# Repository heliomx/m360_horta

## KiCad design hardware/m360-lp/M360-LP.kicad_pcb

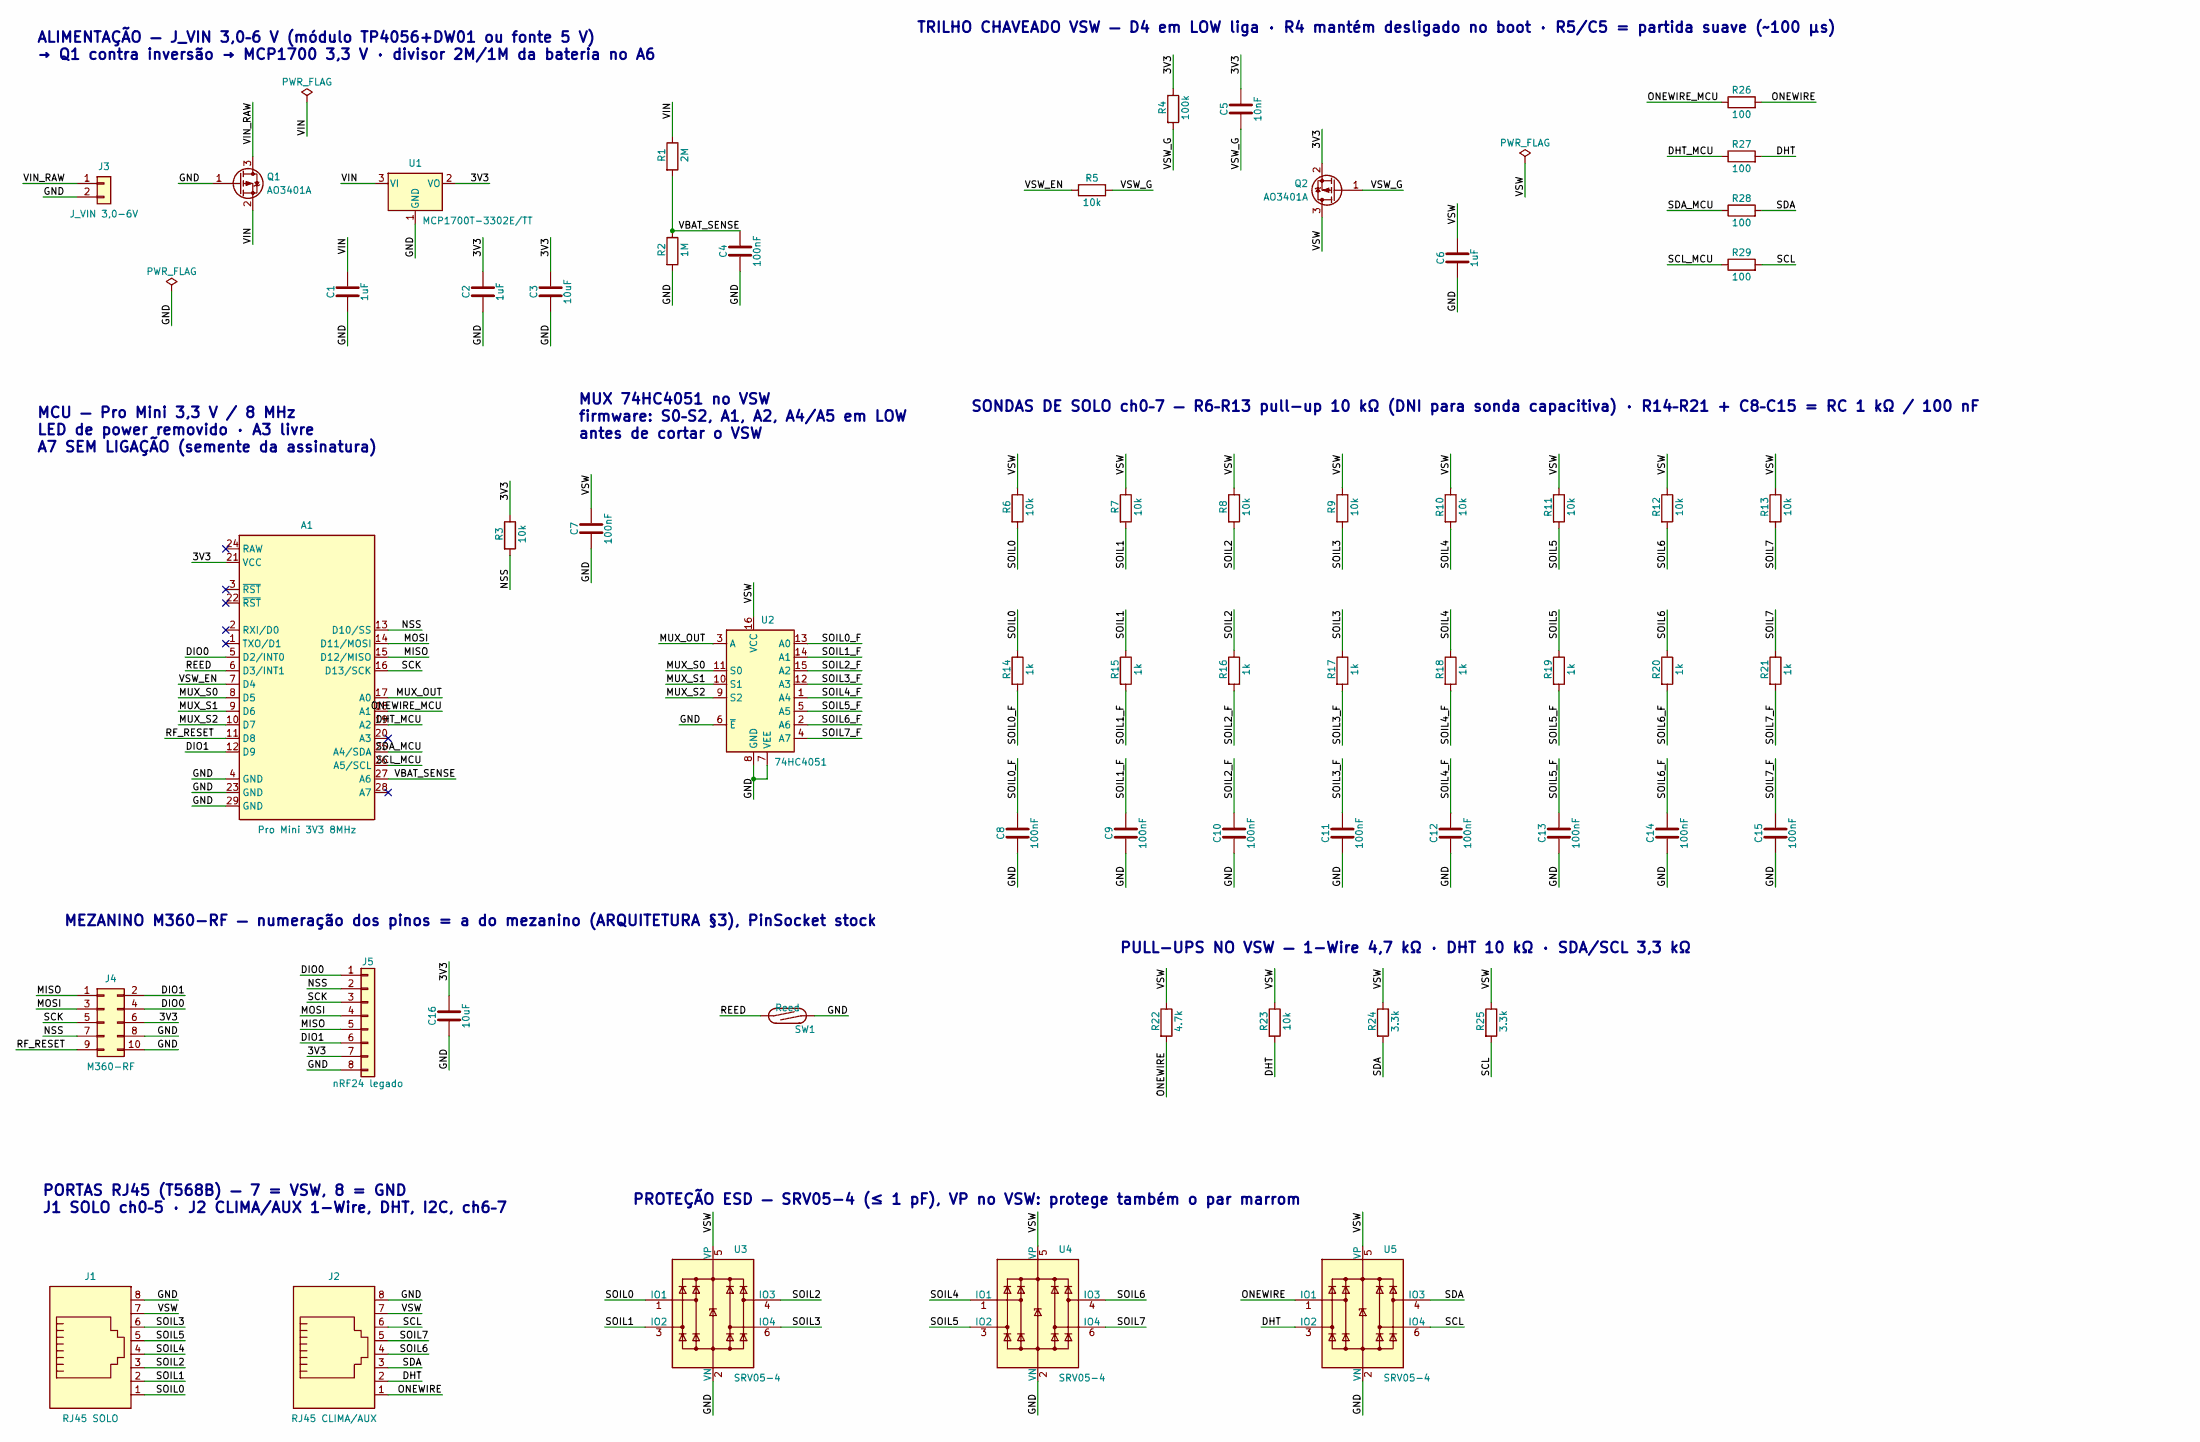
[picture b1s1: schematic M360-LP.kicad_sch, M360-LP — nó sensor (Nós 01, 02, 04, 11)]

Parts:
A1: Pro Mini 3V3 8MHz; Arduino_ProMini_DeeKRobot
C1, C2, C6: 1uF; C_0603_1608Metric; LCSC C15849
C3, C16: 10uF; C_0805_2012Metric; LCSC C15850
C4, C7, C8, C9, C10, C11, C12, C13, C14, C15: 100nF; C_0603_1608Metric; LCSC C14663
C5: 10nF; C_0603_1608Metric; LCSC C57112
J1: RJ45 SOLO; RJ45_R-RJ45R08P-A004; LCSC C385834
J2: RJ45 CLIMA/AUX; RJ45_R-RJ45R08P-A004; LCSC C385834
J3: J_VIN 3,0-6V; JST_XH_B2B-XH-A_1x02_P2.50mm_Vertical; LCSC C158012
J4: M360-RF; M360-RF_Soquete_2x05; LCSC C492399
J5: nRF24 legado; PinHeader_1x08_P2.54mm_Vertical; LCSC C492407
Q1, Q2: AO3401A; SOT-23; LCSC C15127
R1: 2M; R_0603_1608Metric; LCSC C22976
R2: 1M; R_0603_1608Metric; LCSC C22935
R3, R5, R6, R7, R8, R9, R10, R11, R12, R13, R23: 10k; R_0603_1608Metric; LCSC C25804
R4: 100k; R_0603_1608Metric; LCSC C25803
R14, R15, R16, R17, R18, R19, R20, R21: 1k; R_0603_1608Metric; LCSC C21190
R22: 4.7k; R_0603_1608Metric; LCSC C23162
R24, R25: 3.3k; R_0603_1608Metric; LCSC C22978
R26, R27, R28, R29: 100; R_0603_1608Metric; LCSC C22775
SW1: Reed; Reed_Littelfuse_59170; LCSC C315909
U1: MCP1700T-3302E/TT; SOT-23; LCSC C39051
U2: 74HC4051; SOIC-16_3.9x9.9mm_P1.27mm; LCSC C9386
U3, U4, U5: SRV05-4; SOT-23-6; LCSC C558418

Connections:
3V3: A1.21 (VCC), C2.1, C3.1, C5.1, C16.1, J4.6, J5.7, Q2.2 (S), R3.1, R4.1, U1.2 (VO)
DHT: J2.2, R23.2, R27.2, U5.3 (IO2)
DHT_MCU: A1.19 (A2), R27.1
DIO0: A1.5 (D2/INT0), J4.4, J5.1
DIO1: A1.12 (D9), J4.2, J5.6
GND: A1.4 (GND), A1.23 (GND), A1.29 (GND), C1.2, C2.2, C3.2, C4.2, C6.2, C7.2, C8.2, C9.2, C10.2, C11.2, C12.2, C13.2, C14.2, C15.2, C16.2, J1.8, J2.8, J3.2, J4.8, J4.10, J5.8, Q1.1 (G), R2.2, SW1.2, U1.1 (GND), U2.6 (~E), U2.7 (VEE), U2.8 (GND), U3.2 (VN), U4.2 (VN), U5.2 (VN)
MISO: A1.15 (D12/MISO), J4.1, J5.5
MOSI: A1.14 (D11/MOSI), J4.3, J5.4
MUX_OUT: A1.17 (A0), U2.3 (A)
MUX_S0: A1.8 (D5), U2.11 (S0)
MUX_S1: A1.9 (D6), U2.10 (S1)
MUX_S2: A1.10 (D7), U2.9 (S2)
NSS: A1.13 (D10/SS), J4.7, J5.2, R3.2
ONEWIRE: J2.1, R22.2, R26.2, U5.1 (IO1)
ONEWIRE_MCU: A1.18 (A1), R26.1
REED: A1.6 (D3/INT1), SW1.1
RF_RESET: A1.11 (D8), J4.9
SCK: A1.16 (D13/SCK), J4.5, J5.3
SCL: J2.6, R25.2, R29.2, U5.6 (IO4)
SCL_MCU: A1.26 (A5/SCL), R29.1
SDA: J2.3, R24.2, R28.2, U5.4 (IO3)
SDA_MCU: A1.25 (A4/SDA), R28.1
SOIL0: J1.1, R6.2, R14.1, U3.1 (IO1)
SOIL0_F: C8.1, R14.2, U2.13 (A0)
SOIL1: J1.2, R7.2, R15.1, U3.3 (IO2)
SOIL1_F: C9.1, R15.2, U2.14 (A1)
SOIL2: J1.3, R8.2, R16.1, U3.4 (IO3)
SOIL2_F: C10.1, R16.2, U2.15 (A2)
SOIL3: J1.6, R9.2, R17.1, U3.6 (IO4)
SOIL3_F: C11.1, R17.2, U2.12 (A3)
SOIL4: J1.4, R10.2, R18.1, U4.1 (IO1)
SOIL4_F: C12.1, R18.2, U2.1 (A4)
SOIL5: J1.5, R11.2, R19.1, U4.3 (IO2)
SOIL5_F: C13.1, R19.2, U2.5 (A5)
SOIL6: J2.4, R12.2, R20.1, U4.4 (IO3)
SOIL6_F: C14.1, R20.2, U2.2 (A6)
SOIL7: J2.5, R13.2, R21.1, U4.6 (IO4)
SOIL7_F: C15.1, R21.2, U2.4 (A7)
VBAT_SENSE: A1.27 (A6), C4.1, R1.2, R2.1
VIN: C1.1, Q1.2 (S), R1.1, U1.3 (VI)
VIN_RAW: J3.1, Q1.3 (D)
VSW: C6.1, C7.1, J1.7, J2.7, Q2.3 (D), R6.1, R7.1, R8.1, R9.1, R10.1, R11.1, R12.1, R13.1, R22.1, R23.1, R24.1, R25.1, U2.16 (VCC), U3.5 (VP), U4.5 (VP), U5.5 (VP)
VSW_EN: A1.7 (D4), R5.1
VSW_G: C5.2, Q2.1 (G), R4.2, R5.2

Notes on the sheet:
MEZANINO M360-RF — numeração dos pinos = a do mezanino (ARQUITETURA §3), PinSocket stock
ALIMENTAÇÃO — J_VIN 3,0–6 V (módulo TP4056+DW01 ou fonte 5 V) → Q1 contra inversão → MCP1700 3,3 V · divisor 2M/1M da bateria no A6
SONDAS DE SOLO ch0–7 — R6–R13 pull-up 10 kΩ (DNI para sonda capacitiva) · R14–R21 + C8–C15 = RC 1 kΩ / 100 nF
PROTEÇÃO ESD — SRV05-4 (≤ 1 pF), VP no VSW: protege também o par marrom
PULL-UPS NO VSW — 1-Wire 4,7 kΩ · DHT 10 kΩ · SDA/SCL 3,3 kΩ
PORTAS RJ45 (T568B) — 7 = VSW, 8 = GND J1 SOLO ch0–5 · J2 CLIMA/AUX 1-Wire, DHT, I2C, ch6–7
MCU — Pro Mini 3,3 V / 8 MHz LED de power removido · A3 livre A7 SEM LIGAÇÃO (semente da assinatura)
MUX 74HC4051 no VSW firmware: S0–S2, A1, A2, A4/A5 em LOW antes de cortar o VSW
TRILHO CHAVEADO VSW — D4 em LOW liga · R4 mantém desligado no boot · R5/C5 = partida suave (~100 µs)

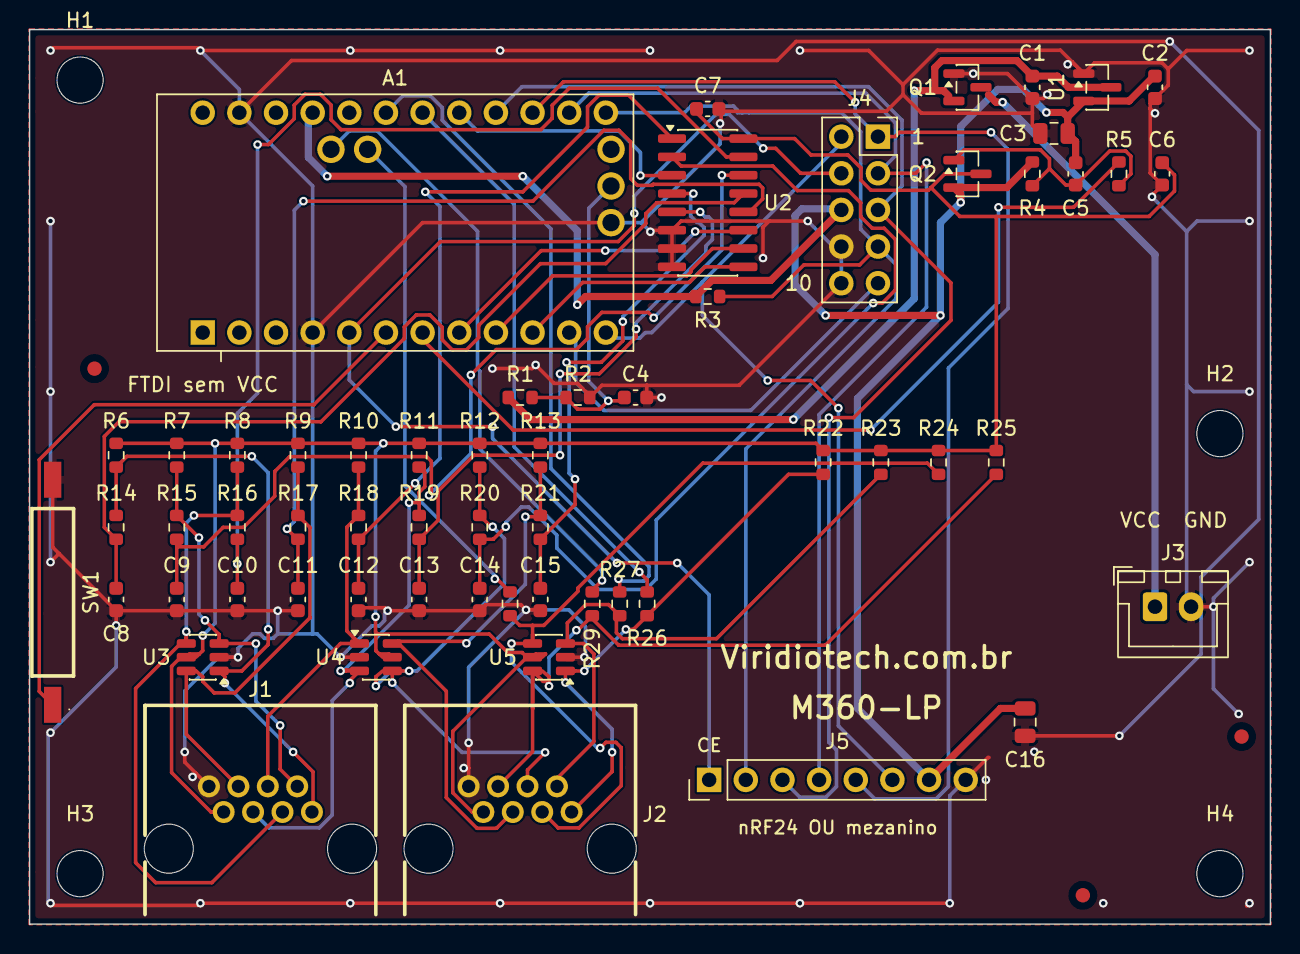
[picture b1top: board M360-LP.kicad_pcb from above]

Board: 2 copper layers, 86.0 x 62.0 mm, 66 parts (0 on the bottom side), 44 nets.

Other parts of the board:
FID1, FID2, FID3: Fiducial_1mm_Mask2mm
H1, H2, H3, H4: MountingHole_3.2mm_M3

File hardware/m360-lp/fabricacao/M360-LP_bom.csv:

Comment,Designator,Footprint,LCSC Part #
1uF,"C1,C2,C6",C_0603_1608Metric,C15849
10uF,"C3,C16",C_0805_2012Metric,C15850
100nF,"C4,C7,C8,C9,C10,C11,C12,C13,C14,C15",C_0603_1608Metric,C14663
10nF,C5,C_0603_1608Metric,C57112
AO3401A,"Q1,Q2",SOT-23,C15127
2M,R1,R_0603_1608Metric,C22976
1M,R2,R_0603_1608Metric,C22935
10k,"R3,R5,R6,R7,R8,R9,R10,R11,R12,R13,R23",R_0603_1608Metric,C25804
100k,R4,R_0603_1608Metric,C25803
1k,"R14,R15,R16,R17,R18,R19,R20,R21",R_0603_1608Metric,C21190
4.7k,R22,R_0603_1608Metric,C23162
3.3k,"R24,R25",R_0603_1608Metric,C22978
100,"R26,R27,R28,R29",R_0603_1608Metric,C22775
Reed,SW1,Reed_Littelfuse_59170,C315909
MCP1700T-3302E/TT,U1,SOT-23,C39051
74HC4051,U2,SOIC-16_3.9x9.9mm_P1.27mm,C9386
SRV05-4,"U3,U4,U5",SOT-23-6,C558418

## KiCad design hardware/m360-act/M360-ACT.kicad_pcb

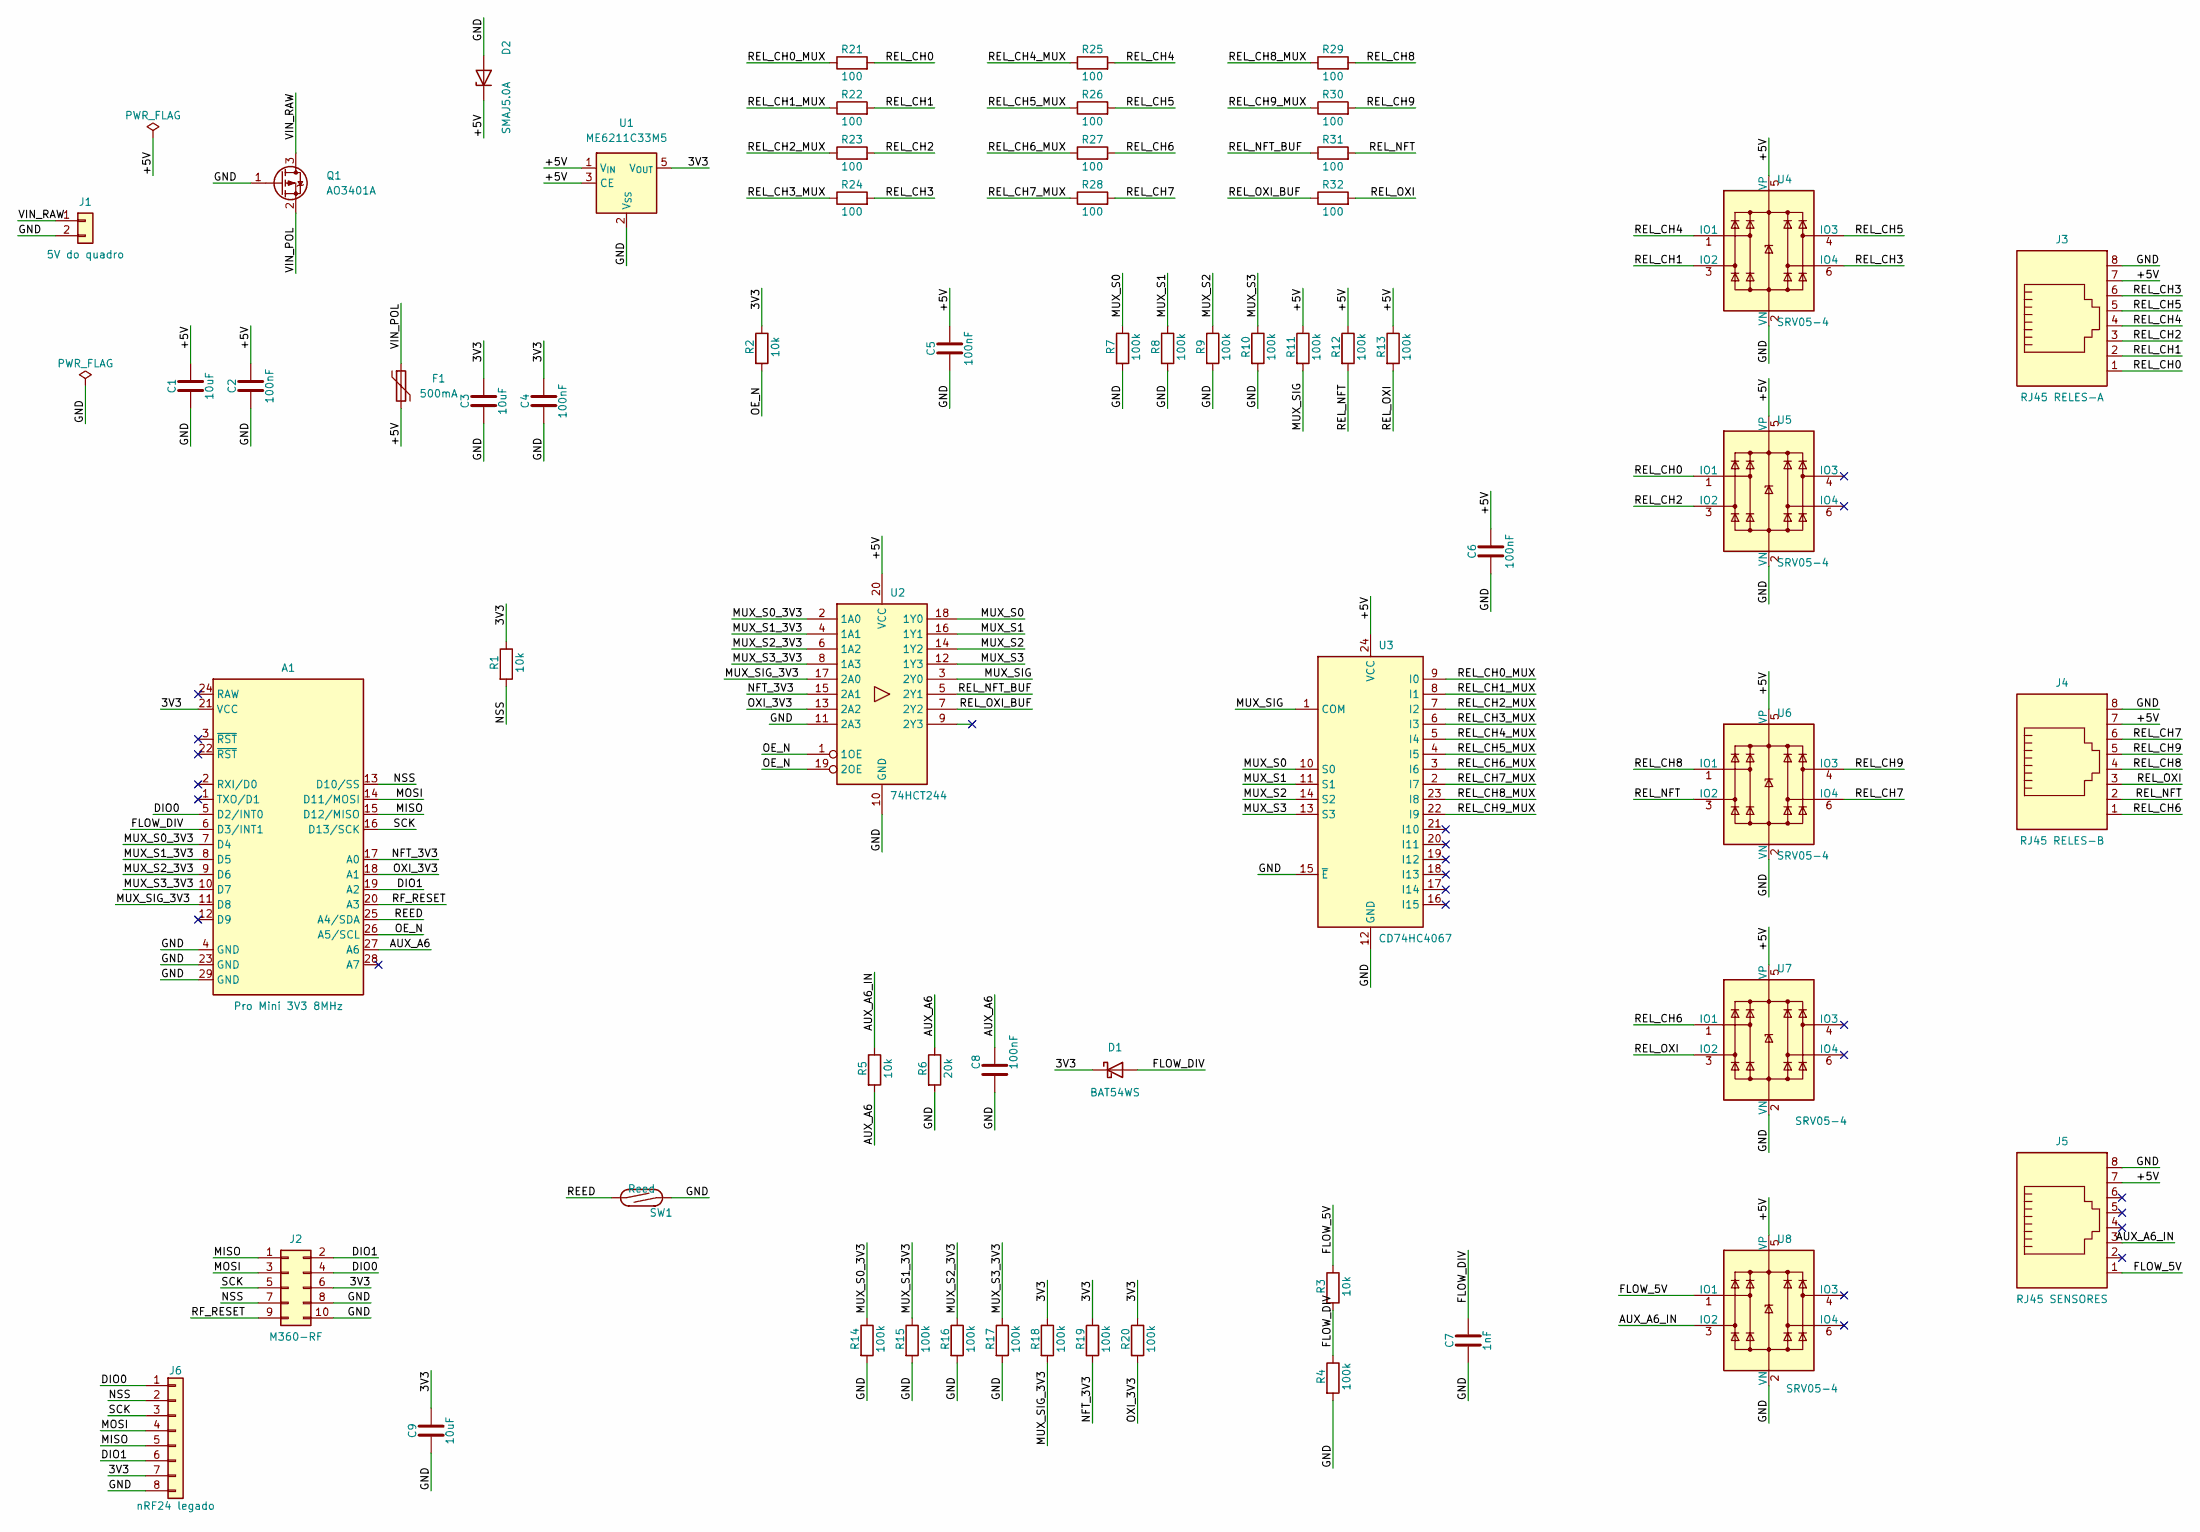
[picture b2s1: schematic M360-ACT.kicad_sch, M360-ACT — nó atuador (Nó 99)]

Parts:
A1: Pro Mini 3V3 8MHz; Arduino_ProMini_DeeKRobot
C1, C3, C9: 10uF; C_0805_2012Metric; LCSC C15850
C2, C4, C5, C6, C8: 100nF; C_0603_1608Metric; LCSC C14663
C7: 1nF; C_0603_1608Metric; LCSC C1588
D1: BAT54WS; D_SOD-323; LCSC C7502694
D2: SMAJ5.0A; D_SMA; LCSC C2925443
F1: 500mA; Fuse_1206_3216Metric; LCSC C720075
J1: 5V do quadro; TerminalBlock_WJ500V-5.08-2P; LCSC C8465
J2: M360-RF; M360-RF_Soquete_2x05; LCSC C492399
J3: RJ45 RELES-A; RJ45_R-RJ45R08P-A004; LCSC C385834
J4: RJ45 RELES-B; RJ45_R-RJ45R08P-A004; LCSC C385834
J5: RJ45 SENSORES; RJ45_R-RJ45R08P-A004; LCSC C385834
J6: nRF24 legado; PinHeader_1x08_P2.54mm_Vertical; LCSC C492407
Q1: AO3401A; SOT-23; LCSC C15127
R1, R2, R3, R5: 10k; R_0603_1608Metric; LCSC C25804
R4, R7, R8, R9, R10, R11, R12, R13, R14, R15, R16, R17, R18, R19, R20: 100k; R_0603_1608Metric; LCSC C25803
R6: 20k; R_0603_1608Metric; LCSC C4184
R21, R22, R23, R24, R25, R26, R27, R28, R29, R30, R31, R32: 100; R_0603_1608Metric; LCSC C22775
SW1: Reed; Reed_Littelfuse_59170; LCSC C315909
U1: ME6211C33M5; SOT-23-5; LCSC C82942
U2: 74HCT244; SOIC-20W_7.5x12.8mm_P1.27mm; LCSC C5978
U3: CD74HC4067; SOIC-24W_7.5x15.4mm_P1.27mm; LCSC C496123
U4, U5, U6, U7, U8: SRV05-4; SOT-23-6; LCSC C558418

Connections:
3V3: A1.21 (VCC), C3.1, C4.1, C9.1, D1.1 (K), J2.6, J6.7, R1.1, R2.1, R18.1, R19.1, R20.1, U1.5 (V_{OUT})
+5V: C1.1, C2.1, C5.1, C6.1, D2.1 (K), F1.2, J3.7, J4.7, J5.7, R11.1, R12.1, R13.1, U1.1 (V_{IN}), U1.3 (CE), U2.20 (VCC), U3.24 (VCC), U4.5 (VP), U5.5 (VP), U6.5 (VP), U7.5 (VP), U8.5 (VP)
AUX_A6: A1.27 (A6), C8.1, R5.2, R6.1
AUX_A6_IN: J5.3, R5.1, U8.3 (IO2)
DIO0: A1.5 (D2/INT0), J2.4, J6.1
DIO1: A1.19 (A2), J2.2, J6.6
FLOW_5V: J5.1, R3.1, U8.1 (IO1)
FLOW_DIV: A1.6 (D3/INT1), C7.1, D1.2 (A), R3.2, R4.1
GND: A1.4 (GND), A1.23 (GND), A1.29 (GND), C1.2, C2.2, C3.2, C4.2, C5.2, C6.2, C7.2, C8.2, C9.2, D2.2 (A), J1.2, J2.8, J2.10, J3.8, J4.8, J5.8, J6.8, Q1.1 (G), R4.2, R6.2, R7.2, R8.2, R9.2, R10.2, R14.2, R15.2, R16.2, R17.2, SW1.2, U1.2 (V_{SS}), U2.10 (GND), U2.11 (2A3), U3.12 (GND), U3.15 (~E), U4.2 (VN), U5.2 (VN), U6.2 (VN), U7.2 (VN), U8.2 (VN)
MISO: A1.15 (D12/MISO), J2.1, J6.5
MOSI: A1.14 (D11/MOSI), J2.3, J6.4
MUX_S0: R7.1, U2.18 (1Y0), U3.10 (S0)
MUX_S0_3V3: A1.7 (D4), R14.1, U2.2 (1A0)
MUX_S1: R8.1, U2.16 (1Y1), U3.11 (S1)
MUX_S1_3V3: A1.8 (D5), R15.1, U2.4 (1A1)
MUX_S2: R9.1, U2.14 (1Y2), U3.14 (S2)
MUX_S2_3V3: A1.9 (D6), R16.1, U2.6 (1A2)
MUX_S3: R10.1, U2.12 (1Y3), U3.13 (S3)
MUX_S3_3V3: A1.10 (D7), R17.1, U2.8 (1A3)
MUX_SIG: R11.2, U2.3 (2Y0), U3.1 (COM)
MUX_SIG_3V3: A1.11 (D8), R18.2, U2.17 (2A0)
NFT_3V3: A1.17 (A0), R19.2, U2.15 (2A1)
NSS: A1.13 (D10/SS), J2.7, J6.2, R1.2
OE_N: A1.26 (A5/SCL), R2.2, U2.1 (1OE), U2.19 (2OE)
OXI_3V3: A1.18 (A1), R20.2, U2.13 (2A2)
REED: A1.25 (A4/SDA), SW1.1
REL_CH0: J3.1, R21.2, U5.1 (IO1)
REL_CH0_MUX: R21.1, U3.9 (I0)
REL_CH1: J3.2, R22.2, U4.3 (IO2)
REL_CH1_MUX: R22.1, U3.8 (I1)
REL_CH2: J3.3, R23.2, U5.3 (IO2)
REL_CH2_MUX: R23.1, U3.7 (I2)
REL_CH3: J3.6, R24.2, U4.6 (IO4)
REL_CH3_MUX: R24.1, U3.6 (I3)
REL_CH4: J3.4, R25.2, U4.1 (IO1)
REL_CH4_MUX: R25.1, U3.5 (I4)
REL_CH5: J3.5, R26.2, U4.4 (IO3)
REL_CH5_MUX: R26.1, U3.4 (I5)
REL_CH6: J4.1, R27.2, U7.1 (IO1)
REL_CH6_MUX: R27.1, U3.3 (I6)
REL_CH7: J4.6, R28.2, U6.6 (IO4)
REL_CH7_MUX: R28.1, U3.2 (I7)
REL_CH8: J4.4, R29.2, U6.1 (IO1)
REL_CH8_MUX: R29.1, U3.23 (I8)
REL_CH9: J4.5, R30.2, U6.4 (IO3)
REL_CH9_MUX: R30.1, U3.22 (I9)
REL_NFT: J4.2, R12.2, R31.2, U6.3 (IO2)
REL_NFT_BUF: R31.1, U2.5 (2Y1)
REL_OXI: J4.3, R13.2, R32.2, U7.3 (IO2)
REL_OXI_BUF: R32.1, U2.7 (2Y2)
RF_RESET: A1.20 (A3), J2.9
SCK: A1.16 (D13/SCK), J2.5, J6.3
VIN_POL: F1.1, Q1.2 (S)
VIN_RAW: J1.1, Q1.3 (D)

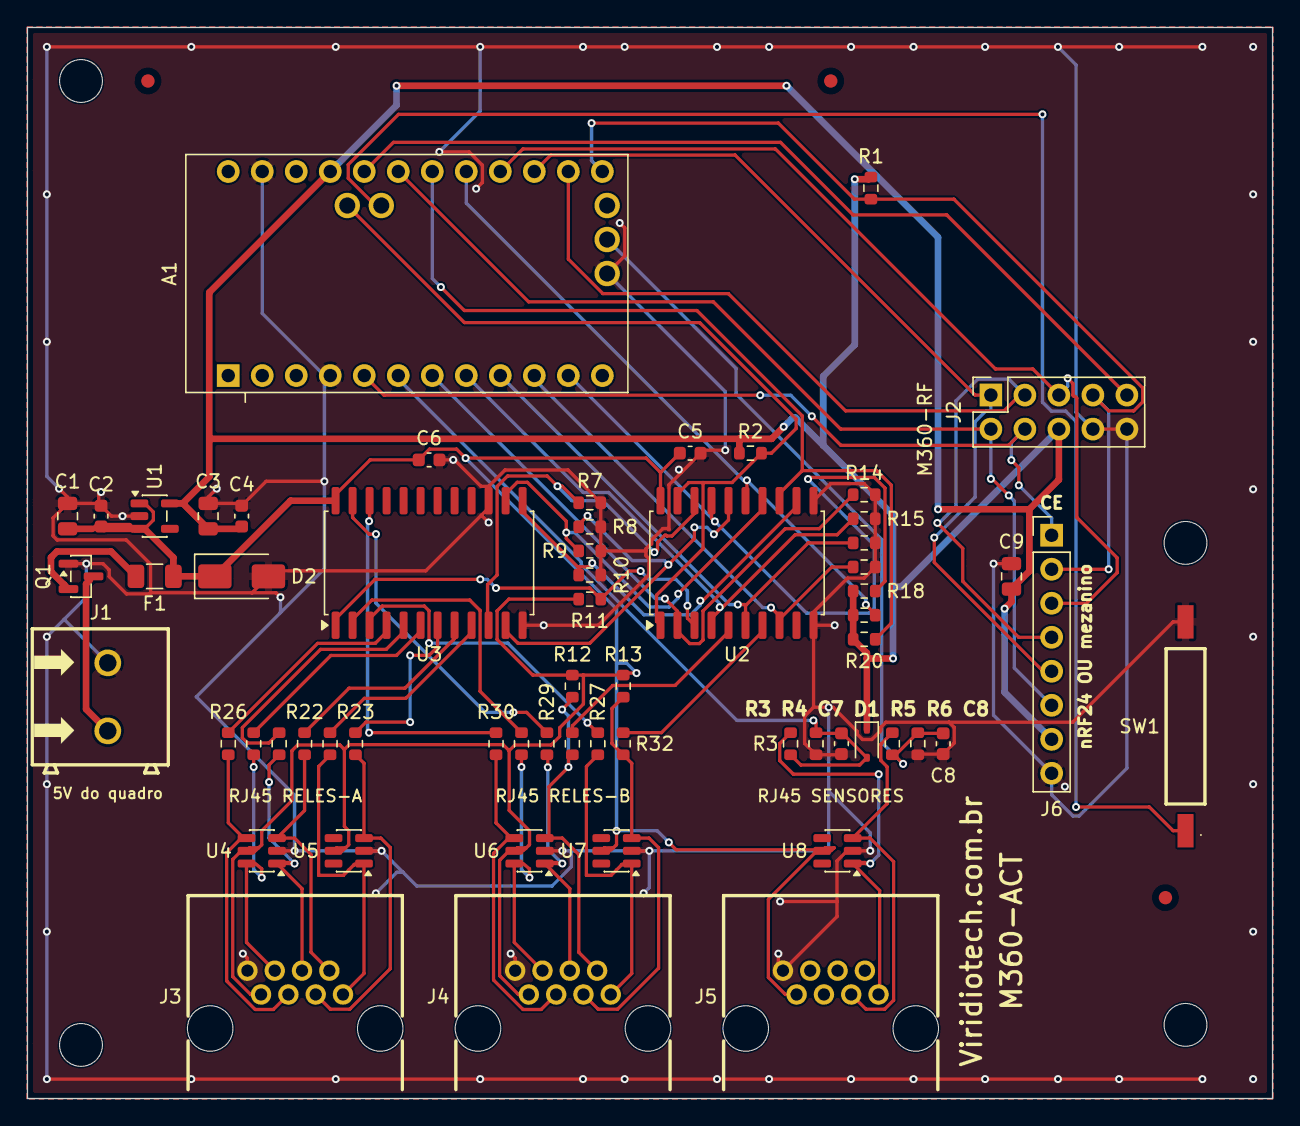
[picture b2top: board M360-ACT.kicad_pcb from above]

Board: 2 copper layers, 93.0 x 80.0 mm, 68 parts (0 on the bottom side), 54 nets.

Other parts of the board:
FID1, FID2, FID3: Fiducial_1mm_Mask2mm
H1, H2, H3, H4: MountingHole_3.2mm_M3

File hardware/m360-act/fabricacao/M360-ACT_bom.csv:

Comment,Designator,Footprint,LCSC Part #
10uF,"C1,C3,C9",C_0805_2012Metric,C15850
100nF,"C2,C4,C5,C6,C8",C_0603_1608Metric,C14663
1nF,C7,C_0603_1608Metric,C1588
BAT54WS,D1,D_SOD-323,C7502694
SMAJ5.0A,D2,D_SMA,C2925443
500mA,F1,Fuse_1206_3216Metric,C720075
AO3401A,Q1,SOT-23,C15127
10k,"R1,R2,R3,R5",R_0603_1608Metric,C25804
100k,"R4,R7,R8,R9,R10,R11,R12,R13,R14,R15,R16,R17,R18,R19,R20",R_0603_1608Metric,C25803
20k,R6,R_0603_1608Metric,C4184
100,"R21,R22,R23,R24,R25,R26,R27,R28,R29,R30,R31,R32",R_0603_1608Metric,C22775
Reed,SW1,Reed_Littelfuse_59170,C315909
ME6211C33M5,U1,SOT-23-5,C82942
74HCT244,U2,SOIC-20W_7.5x12.8mm_P1.27mm,C5978
CD74HC4067,U3,SOIC-24W_7.5x15.4mm_P1.27mm,C496123
SRV05-4,"U4,U5,U6,U7,U8",SOT-23-6,C558418

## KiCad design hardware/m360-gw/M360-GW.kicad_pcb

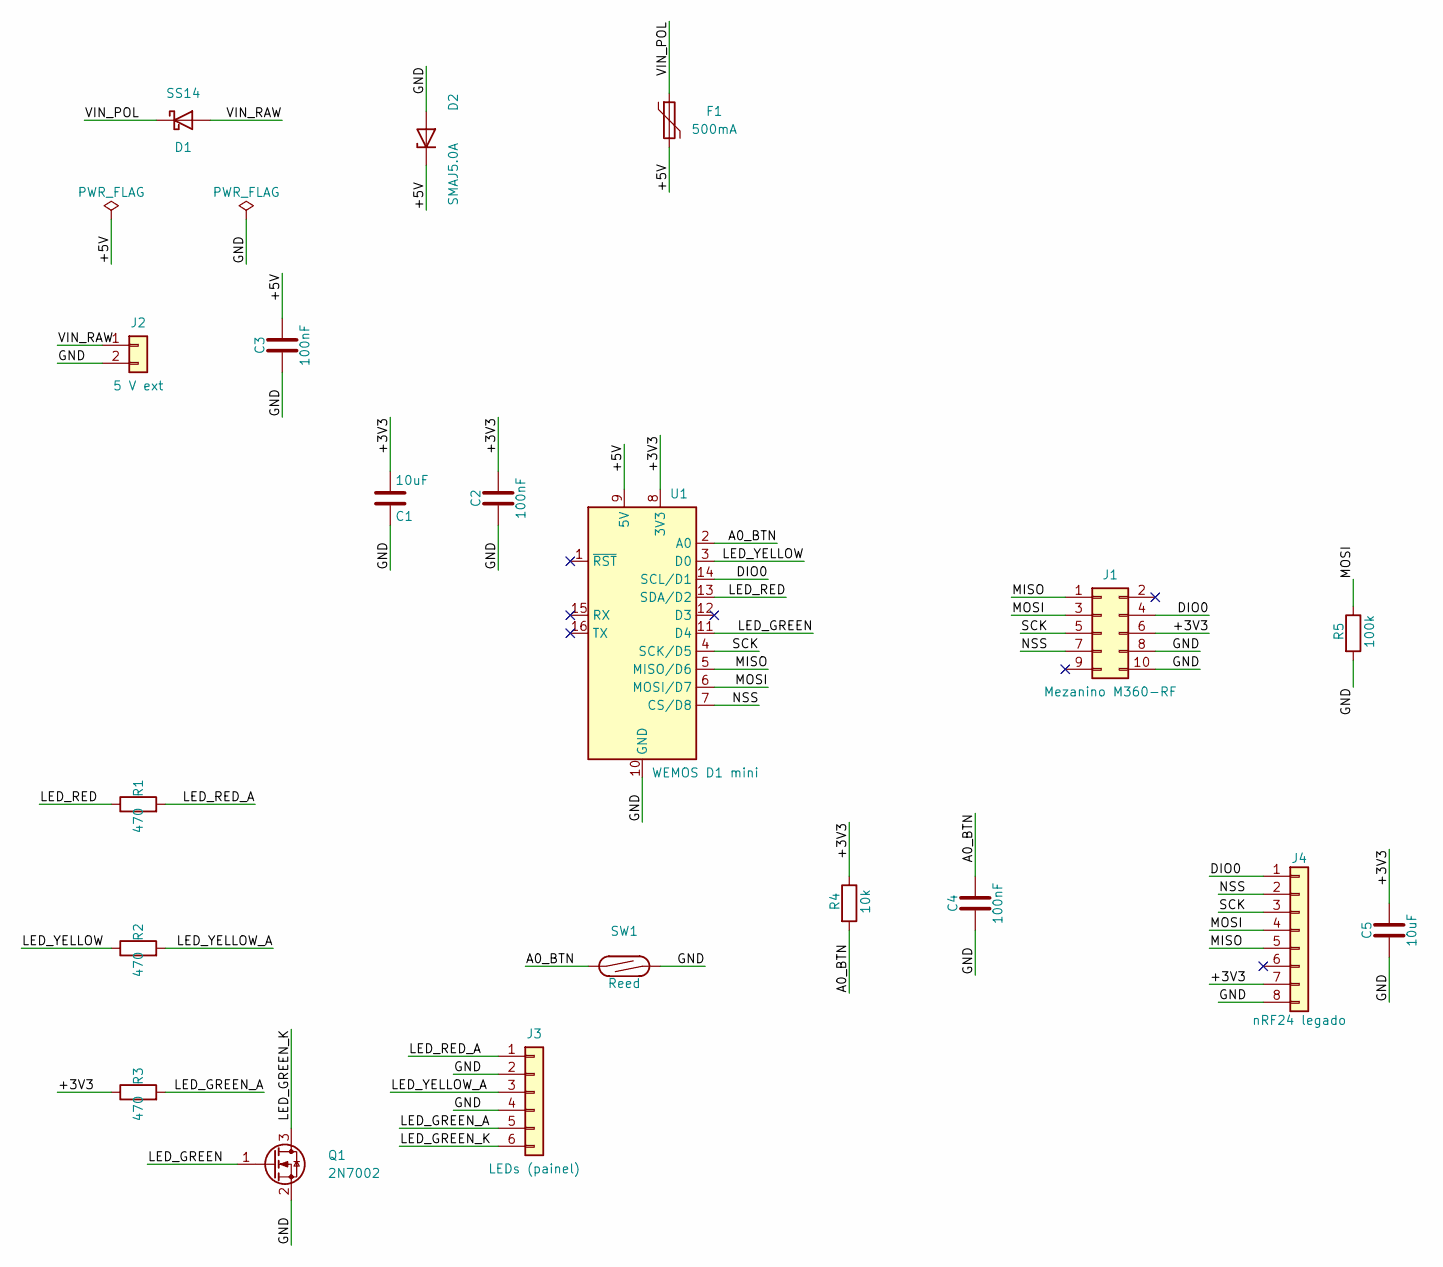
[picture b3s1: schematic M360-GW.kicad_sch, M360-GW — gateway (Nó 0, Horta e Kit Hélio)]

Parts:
C1, C5: 10uF; C_0805_2012Metric; LCSC C15850
C2, C3, C4: 100nF; C_0603_1608Metric; LCSC C14663
D1: SS14; D_SMA; LCSC C2480
D2: SMAJ5.0A; D_SMA; LCSC C2925443
F1: 500mA; Fuse_1206_3216Metric; LCSC C720075
FLG1, FLG2: PWR_FLAG
J1: Mezanino M360-RF; M360-RF_Soquete_2x05; LCSC C492399
J2: 5 V ext; TerminalBlock_WJ500V-5.08-2P; LCSC C8465
J3: LEDs (painel); JST_XH_B6B-XH-A_1x06_P2.50mm_Vertical; LCSC C144397
J4: nRF24 legado; PinHeader_1x08_P2.54mm_Vertical; LCSC C492407
Q1: 2N7002; SOT-23; LCSC C8545
R1, R2, R3: 470; R_0603_1608Metric; LCSC C23179
R4: 10k; R_0603_1608Metric; LCSC C25804
R5: 100k; R_0603_1608Metric; LCSC C25803
SW1: Reed; Reed_Littelfuse_59170; LCSC C315909
U1: WEMOS D1 mini; WEMOS_D1_mini_light

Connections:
+3V3: C1.1, C2.1, C5.1, J1.6, J4.7, R3.1, R4.1, U1.8 (3V3)
+5V: C3.1, D2.1 (K), F1.2, FLG1.1, U1.9 (5V)
A0_BTN: C4.1, R4.2, SW1.1, U1.2 (A0)
DIO0: J1.4, J4.1, U1.14 (SCL/D1)
GND: C1.2, C2.2, C3.2, C4.2, C5.2, D2.2 (A), FLG2.1, J1.8, J1.10, J2.2, J3.2, J3.4, J4.8, Q1.2 (S), R5.2, SW1.2, U1.10 (GND)
LED_GREEN: Q1.1 (G), U1.11 (D4)
LED_GREEN_A: J3.5, R3.2
LED_GREEN_K: J3.6, Q1.3 (D)
LED_RED: R1.1, U1.13 (SDA/D2)
LED_RED_A: J3.1, R1.2
LED_YELLOW: R2.1, U1.3 (D0)
LED_YELLOW_A: J3.3, R2.2
MISO: J1.1, J4.5, U1.5 (MISO/D6)
MOSI: J1.3, J4.4, R5.1, U1.6 (MOSI/D7)
NSS: J1.7, J4.2, U1.7 (CS/D8)
SCK: J1.5, J4.3, U1.4 (SCK/D5)
VIN_POL: D1.1 (K), F1.1
VIN_RAW: D1.2 (A), J2.1

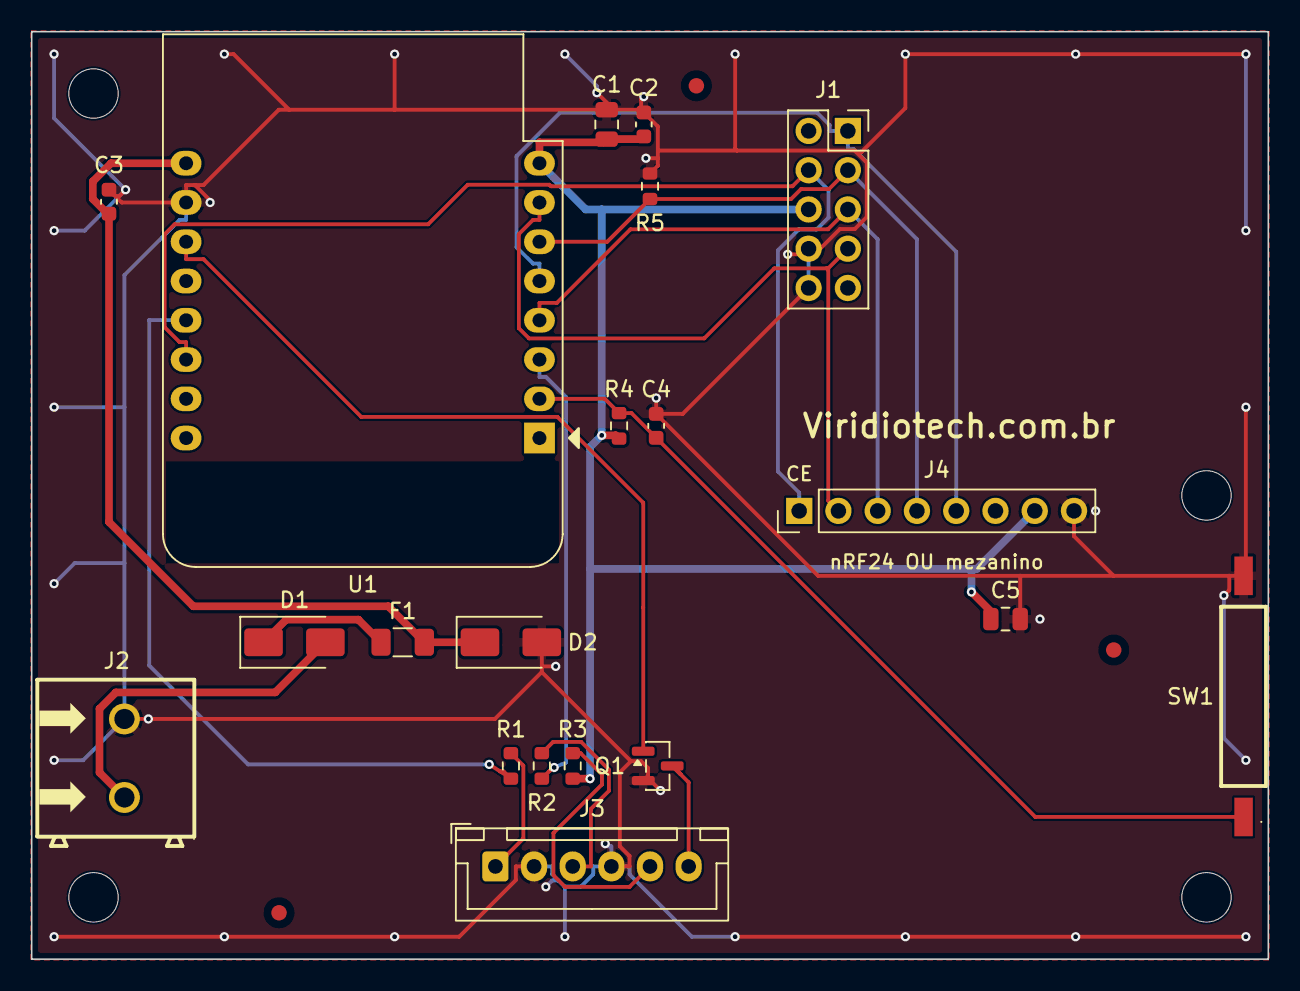
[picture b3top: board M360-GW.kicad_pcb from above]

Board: 2 copper layers, 80.0 x 60.0 mm, 27 parts (0 on the bottom side), 18 nets.

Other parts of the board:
FID1, FID2, FID3: Fiducial_1mm_Mask2mm
H1, H2, H3, H4: MountingHole_3.2mm_M3

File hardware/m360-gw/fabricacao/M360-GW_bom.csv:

Comment,Designator,Footprint,LCSC Part #
10uF,"C1,C5",C_0805_2012Metric,C15850
100nF,"C2,C3,C4",C_0603_1608Metric,C14663
SS14,D1,D_SMA,C2480
SMAJ5.0A,D2,D_SMA,C2925443
500mA,F1,Fuse_1206_3216Metric,C720075
2N7002,Q1,SOT-23,C8545
470,"R1,R2,R3",R_0603_1608Metric,C23179
10k,R4,R_0603_1608Metric,C25804
100k,R5,R_0603_1608Metric,C25803
Reed,SW1,Reed_Littelfuse_59170,C315909

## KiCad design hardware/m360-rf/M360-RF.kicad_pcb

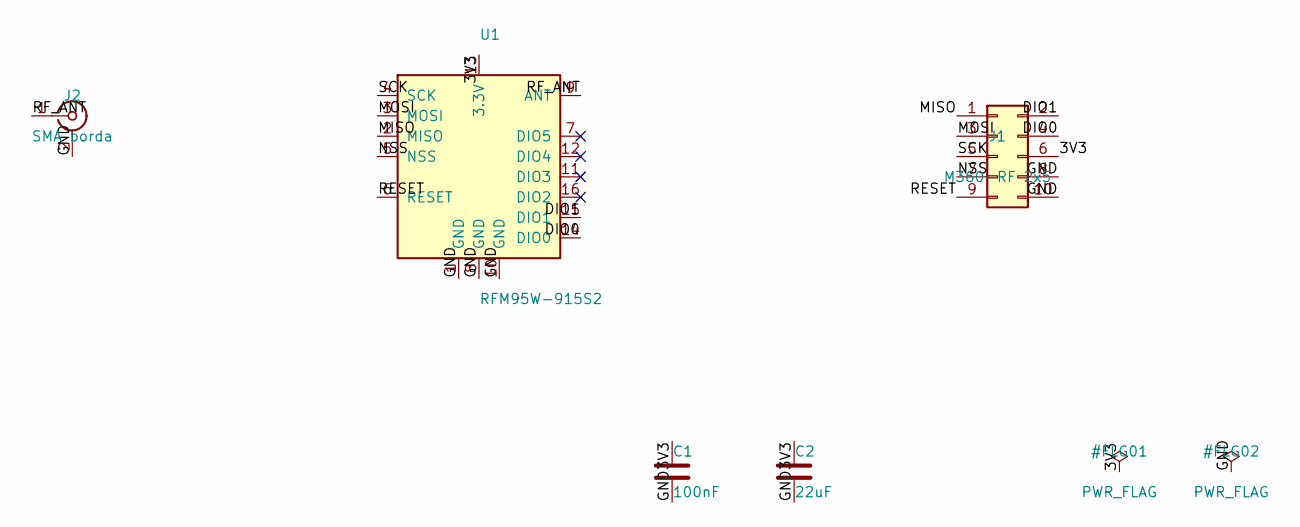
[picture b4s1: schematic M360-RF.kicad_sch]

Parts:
C1: 100nF; C_0603_1608Metric; LCSC C14663
C2: 22uF; C_0805_2012Metric; LCSC C45783
J1: M360-RF 2x5; PinHeader_2x05_P2.54mm_Vertical; LCSC C492422
J2: SMA borda; SMA_Samtec_SMA-J-P-H-ST-EM1_EdgeMount; MPN SMA-J-P-H-ST-EM1; LCSC C5199907
U1: RFM95W-915S2; HOPERF_RFM9XW_SMD; MPN RFM95W-915S2

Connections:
3V3: C1.1, C2.1, J1.6, U1.13 (3.3V)
DIO0: J1.4, U1.14 (DIO0)
DIO1: J1.2, U1.15 (DIO1)
GND: C1.2, C2.2, J1.8, J1.10, J2.2 (Ext), U1.1 (GND), U1.8 (GND), U1.10 (GND)
MISO: J1.1, U1.2 (MISO)
MOSI: J1.3, U1.3 (MOSI)
NSS: J1.7, U1.5 (NSS)
RESET: J1.9, U1.6 (RESET)
RF_ANT: J2.1 (In), U1.9 (ANT)
SCK: J1.5, U1.4 (SCK)

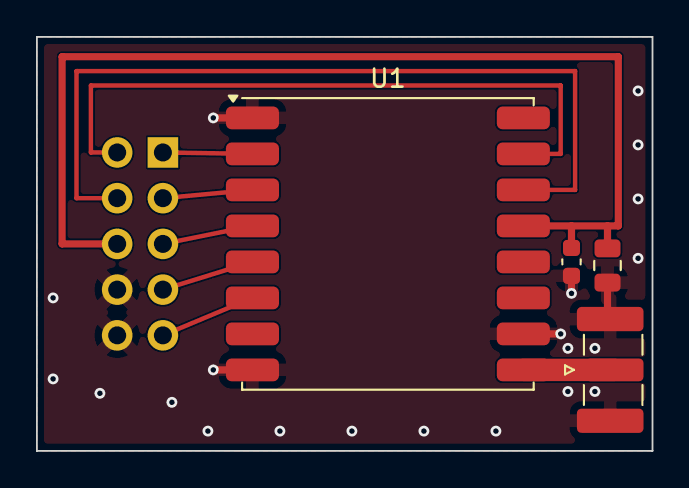
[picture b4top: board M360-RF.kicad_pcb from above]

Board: 2 copper layers, 34.2 x 23.0 mm, 5 parts (1 on the bottom side), 10 nets.

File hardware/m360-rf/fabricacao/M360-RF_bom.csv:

Comment,Designator,Footprint,LCSC Part #
100nF,C1,C_0603_1608Metric,C14663
22uF,C2,C_0805_2012Metric,C45783
SMA borda,J2,SMA_Samtec_SMA-J-P-H-ST-EM1_EdgeMount,C5199907
